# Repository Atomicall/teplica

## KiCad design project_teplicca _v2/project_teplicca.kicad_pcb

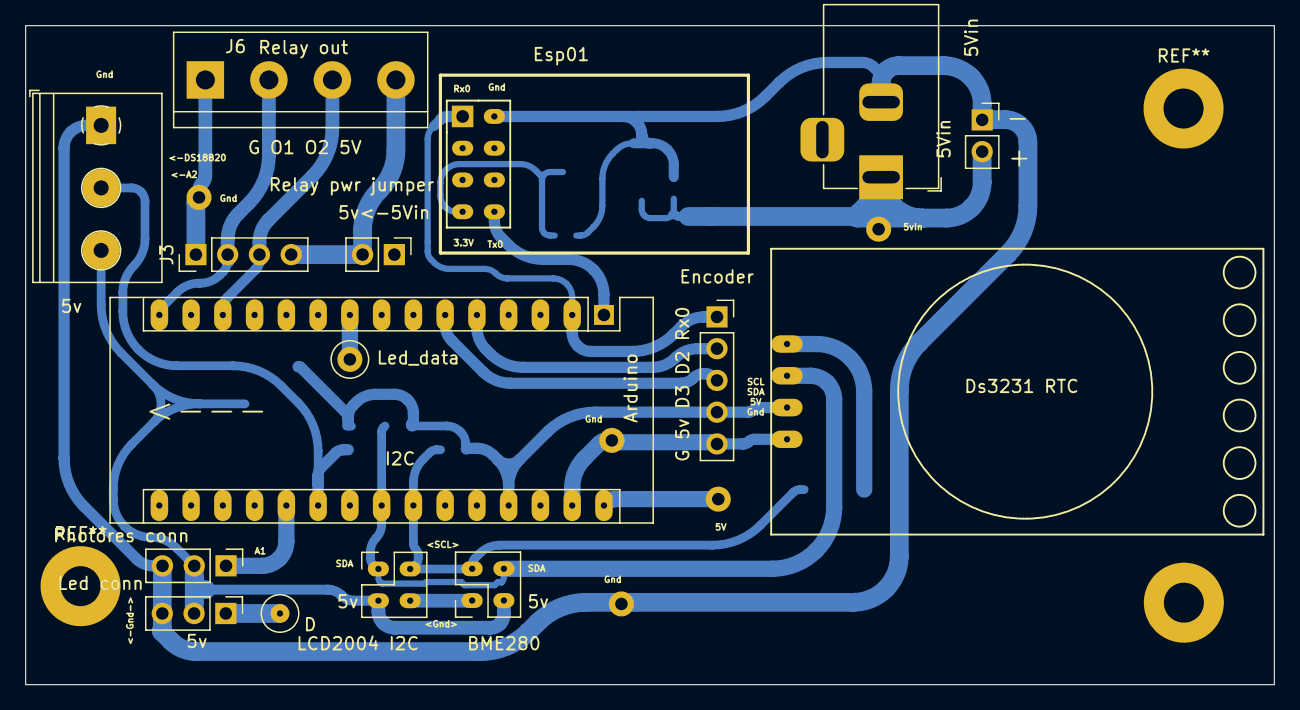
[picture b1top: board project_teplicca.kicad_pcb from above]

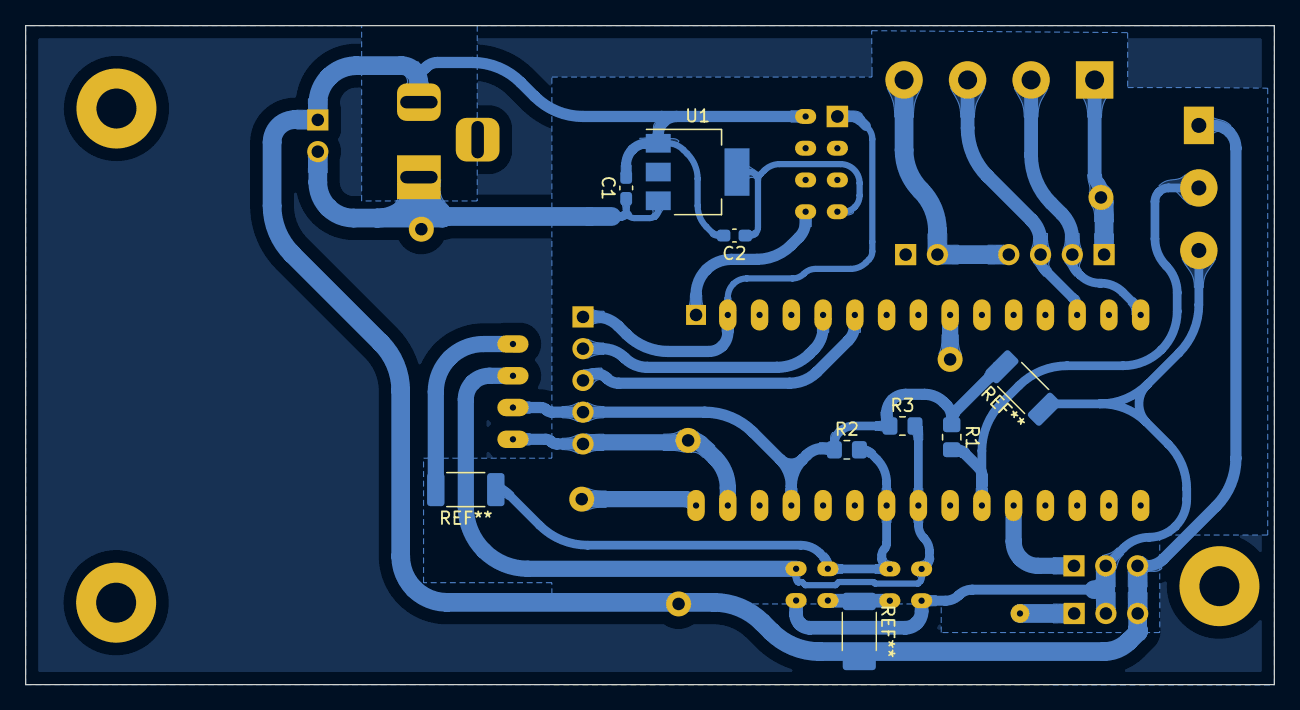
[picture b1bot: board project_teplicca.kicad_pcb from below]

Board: 2 copper layers, 99.9 x 52.7 mm, 22 parts (6 on the bottom side), 16 nets.

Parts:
5Vin: PinSocket_1x02_P2.54mm_Vertical
5Vin#2: Jack-DC; BarrelJack_Horizontal
<-DS18B20: DS18B20; TerminalBlock_Philmore_TB133_1x03_P5.00mm_Horizontal
Arduino: Arduino_Nano_v3.x; Arduino_Nano
BME280: BME280_module; PinSocket_2x02_P2.54mm_Vertical
C1: 10uF; C_0603_1608Metric_Pad1.08x0.95mm_HandSolder
C2: 1uF; C_0603_1608Metric_Pad1.08x0.95mm_HandSolder
D: TestPoint_Loop_D1.80mm_Drill1.0mm_Beaded
Ds3231 RTC: RTC_DS3231
Encoder: circle_encoder; PinSocket_1x05_P2.54mm_Vertical
Esp01: ESP-01v090; ESP-01
J3: Relay_conn; PinHeader_1x04_P2.54mm_Vertical
J6: Relay_conn_term; TerminalBlock_bornier-4_P5.08mm
LCD2004 I2C: LCD2004_I2C; PinHeader_2x02_P2.54mm_Vertical
Led conn: Led; PinHeader_1x03_P2.54mm_Vertical
Led_data: TestPoint_Loop_D1.80mm_Drill1.0mm_Beaded
Photores conn: Photoresistor; PinHeader_1x03_P2.54mm_Vertical
R1, R2, R3: 4.7k; R_0805_2012Metric_Pad1.20x1.40mm_HandSolder
Relay pwr jumper: vin->relay_in; PinHeader_1x02_P2.54mm_Vertical
U1: AMS1117-3.3; SOT-223-3_TabPin2

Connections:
5v_Relay: J3.4, J6.4, Relay pwr jumper.2
5v_ardu: <-DS18B20.3 (VDD), Arduino.27 (+5V), BME280.2 (GND), Ds3231 RTC.2 (VCC), Encoder.4 (Key), LCD2004 I2C.3, Led conn.2, Photores conn.2, R1.1, R2.1, R3.1
5v_vin: 5Vin.2, 5Vin#2.1, Arduino.30 (VIN), C1.1, Relay pwr jumper.1, U1.3 (VI)
A1: Arduino.20 (A1), Photores conn.1
A2: <-DS18B20.2 (DQ), Arduino.21 (A2), R1.2
D: Arduino.9 (D6), D.1, Led conn.1, Led_data.1
D2: Arduino.5 (D2), Encoder.2 (S1)
D3: Arduino.6 (D3), Encoder.3 (S2)
D10: Arduino.13 (D10), J3.3, J6.3
D12: Arduino.15 (D12), J3.2, J6.2
GND: 5Vin.1, 5Vin#2.2, <-DS18B20.1 (GND), Arduino.4 (GND), Arduino.29 (GND), BME280.1 (VIN), C1.2, C2.2, Ds3231 RTC.1 (GND), Encoder.5 (VCC), Esp01.2 (GND), J3.1, J6.1, LCD2004 I2C.4, Led conn.3, Photores conn.3, U1.1 (GND)
unnamed: C2.1, Esp01.7 (VCC), U1.2 (VO)
Rx0: Arduino.2 (D0/RX), Encoder.1 (GND), Esp01.1 (UTXD)
SCL: Arduino.24 (A5), BME280.3 (SCL), Ds3231 RTC.4 (SCL), LCD2004 I2C.2, R2.2
SDA: Arduino.23 (A4), BME280.4 (SDA), Ds3231 RTC.3 (SDA), LCD2004 I2C.1, R3.2
Tx1: Arduino.1 (D1/TX), Esp01.8 (URXD)

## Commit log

2022-09-03 PCB v1 done
2022-10-19 Zapiska V1 Scheme V1
2022-10-19 Zapiska V2
2022-10-19 Zapiska v2.1
2022-10-26 SchV2 edited
